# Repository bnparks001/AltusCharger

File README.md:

<div align="center">
  <h1>Altus Charger</h1>
  6 channel output charger for AltusMetrum batteries. 
  
  ## Status
  Boards have arrived and passed testing great!
  <div>
    <h3><em>Assembled Board:</em></h3>
    
  </div>
  
  ## Hardware
  This project is designed to support charging of 6 Altus Metrum batteries over a 5V 2A USB-C connection using the same battery charging circuit as the Telemega. Therefore, the RProg resistor selection was set to 3.3k to charge each battery at ~300mA. For context, the Telemega integrated charger is configured to charge at ~342mA. This results in ~13% slower charging per battery. However, with the benefit of charging multiple batteries at once this quickly makes up the difference.
  This project also includes a switch to turn off the LED indicators for overnight charging. 
  
  ## Schematic
  <h3><em>Root Schematic:</em></h3>
  <p>The root level schematic shows the overall blocking of the hardware design.</p>
  <br>
      
  ## PCB Design
  <div>
    <h3><em>3D Render:</em></h3>

  </div>
  
  <div>
    <h3><em>PCB Artwork:</em></h3>
    
    <br>
  </div>
</div>

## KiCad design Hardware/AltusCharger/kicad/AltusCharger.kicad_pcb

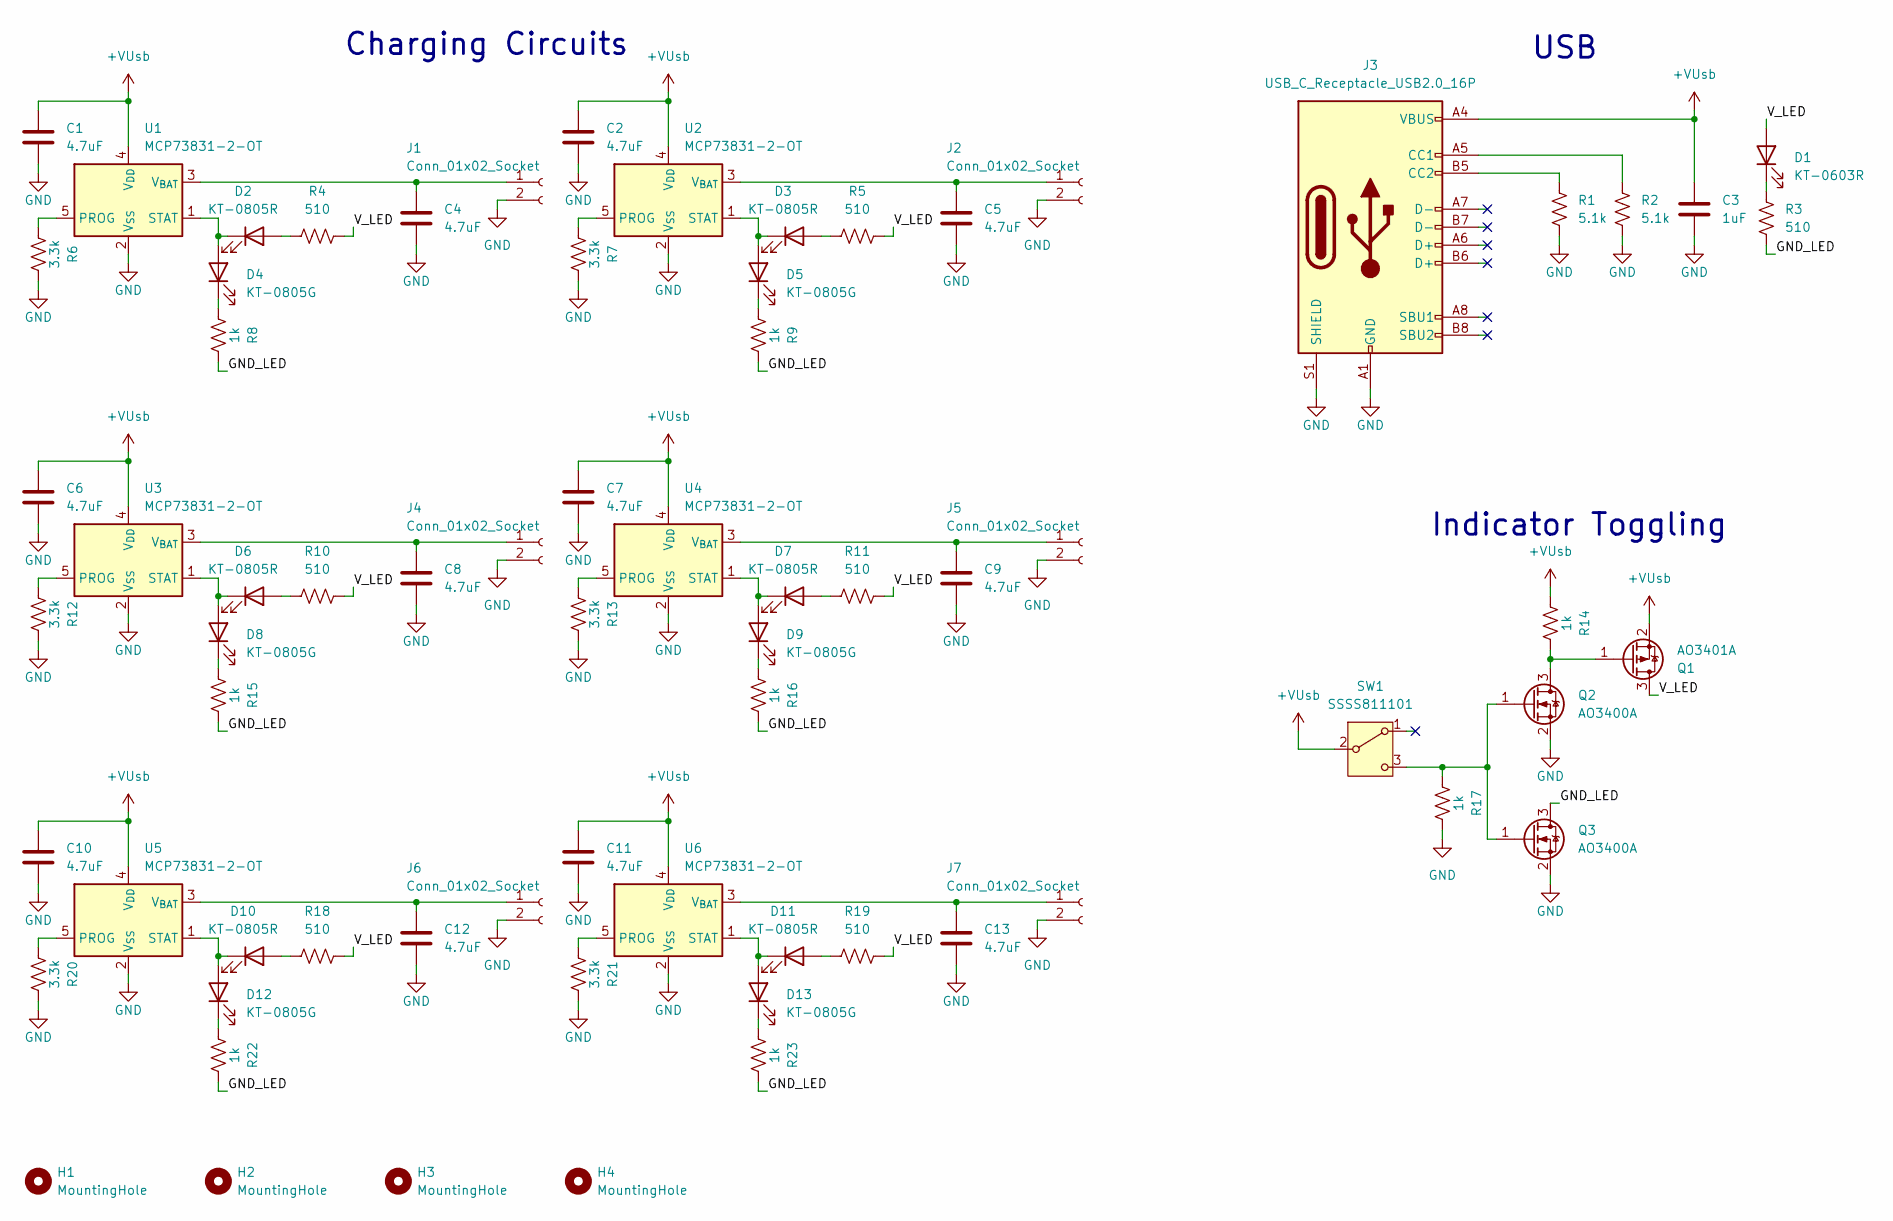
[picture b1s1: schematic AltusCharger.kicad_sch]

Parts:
C1, C2, C4, C5, C6, C7, C8, C9, C10, C11, C12, C13: 4.7uF; C_0402_1005Metric; JLCPCB Part # C23733
C3: 1uF; C_0402_1005Metric; JLCPCB Part # C52923
D1: KT-0603R; LED_0603_1608Metric; JLCPCB Part # C2286
D2, D3, D6, D7, D10, D11: KT-0805R; LED_0805_2012Metric; JLCPCB Part # C2295
D4, D5, D8, D9, D12, D13: KT-0805G; LED_0805_2012Metric; JLCPCB Part # C2297
H1, H2, H3, H4: MountingHole; MountingHole_3.2mm_M3
J1, J2, J4, J5, J6, J7: Conn_01x02_Socket; JST_PH_B2B-PH-K_1x02_P2.00mm_Vertical; JLCPCB Part # C2319
J3: USB_C_Receptacle_USB2.0_16P; USB_C_Receptacle_G-Switch_GT-USB-7010ASV; JLCPCB Part # C2988369
Q1: AO3401A; SOT-23; JLCPCB Part # C15127
Q2, Q3: AO3400A; SOT-23; JLCPCB Part # C20917
R1, R2: 5.1k; R_0402_1005Metric; JLCPCB Part # C25905
R3, R4, R5, R10, R11, R18, R19: 510; R_0402_1005Metric; JLCPCB Part # C25123
R6, R7, R12, R13, R20, R21: 3.3k; R_0402_1005Metric; JLCPCB Part # C25890
R8, R9, R14, R15, R16, R17, R22, R23: 1k; R_0402_1005Metric; JLCPCB Part # C11702
SW1: SSSS811101; SW_SSSS811101; JLCPCB Part # C109335
U1, U2, U3, U4, U5, U6: MCP73831-2-OT; SOT-23-5; JLCPCB Part # C424093

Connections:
+VUsb: C1.1, C2.1, C3.1, C6.1, C7.1, C10.1, C11.1, J3.A4 (VBUS), J3.A9 (VBUS), J3.B4 (VBUS), J3.B9 (VBUS), Q1.2 (S), R14.1, SW1.2 (B), U1.4 (V_{DD}), U2.4 (V_{DD}), U3.4 (V_{DD}), U4.4 (V_{DD}), U5.4 (V_{DD}), U6.4 (V_{DD})
/GND_LED: Q3.3 (D), R3.2, R8.2, R9.2, R15.2, R16.2, R22.2, R23.2
/V_LED: D1.2 (A), Q1.3 (D), R4.2, R5.2, R10.2, R11.2, R18.2, R19.2
GND: C1.2, C2.2, C3.2, C4.2, C5.2, C6.2, C7.2, C8.2, C9.2, C10.2, C11.2, C12.2, C13.2, J1.2, J2.2, J3.A1 (GND), J3.A12 (GND), J3.B1 (GND), J3.B12 (GND), J3.S1 (SHIELD), J4.2, J5.2, J6.2, J7.2, Q2.2 (S), Q3.2 (S), R1.2, R2.2, R6.2, R7.2, R12.2, R13.2, R17.2, R20.2, R21.2, U1.2 (V_{SS}), U2.2 (V_{SS}), U3.2 (V_{SS}), U4.2 (V_{SS}), U5.2 (V_{SS}), U6.2 (V_{SS})
unnamed: D1.1 (K), R3.1
unnamed: D2.2 (A), R4.1
unnamed: D2.1 (K), D4.2 (A), U1.1 (STAT)
unnamed: D3.2 (A), R5.1
unnamed: D3.1 (K), D5.2 (A), U2.1 (STAT)
unnamed: D4.1 (K), R8.1
unnamed: D5.1 (K), R9.1
unnamed: D6.2 (A), R10.1
unnamed: D6.1 (K), D8.2 (A), U3.1 (STAT)
unnamed: D7.2 (A), R11.1
unnamed: D7.1 (K), D9.2 (A), U4.1 (STAT)
unnamed: D8.1 (K), R15.1
unnamed: D9.1 (K), R16.1
unnamed: D10.2 (A), R18.1
unnamed: D10.1 (K), D12.2 (A), U5.1 (STAT)
unnamed: D11.2 (A), R19.1
unnamed: D11.1 (K), D13.2 (A), U6.1 (STAT)
unnamed: D12.1 (K), R22.1
unnamed: D13.1 (K), R23.1
unnamed: C4.1, J1.1, U1.3 (V_{BAT})
unnamed: C5.1, J2.1, U2.3 (V_{BAT})
unnamed: J3.A5 (CC1), R2.1
unnamed: J3.B5 (CC2), R1.1
unnamed: C8.1, J4.1, U3.3 (V_{BAT})
unnamed: C9.1, J5.1, U4.3 (V_{BAT})
unnamed: C12.1, J6.1, U5.3 (V_{BAT})
unnamed: C13.1, J7.1, U6.3 (V_{BAT})
unnamed: Q1.1 (G), Q2.3 (D), R14.2
unnamed: Q2.1 (G), Q3.1 (G), R17.1, SW1.3 (C)
unnamed: R6.1, U1.5 (PROG)
unnamed: R7.1, U2.5 (PROG)
unnamed: R12.1, U3.5 (PROG)
unnamed: R13.1, U4.5 (PROG)
unnamed: R20.1, U5.5 (PROG)
unnamed: R21.1, U6.5 (PROG)

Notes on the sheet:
USB
Charging Circuits
Indicator Toggling

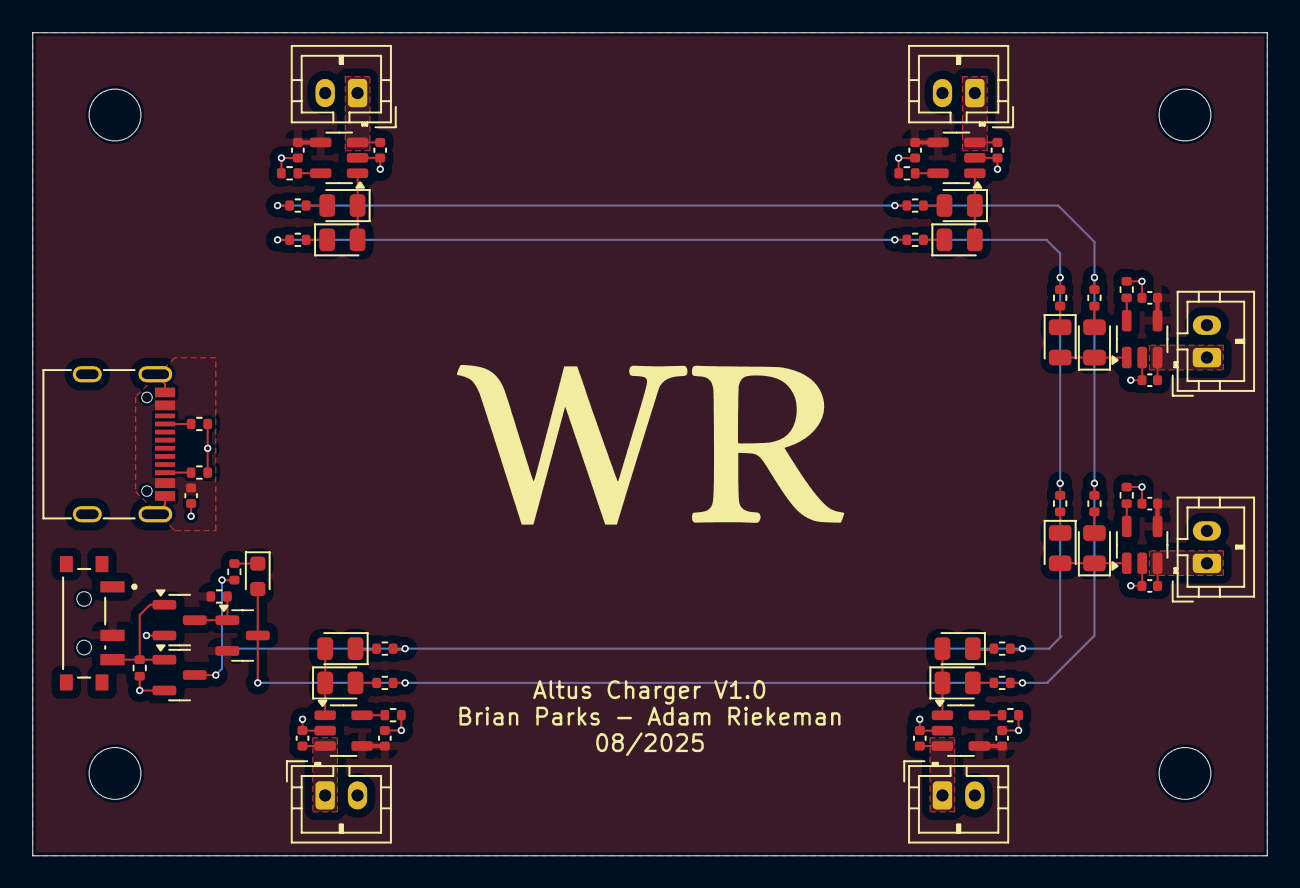
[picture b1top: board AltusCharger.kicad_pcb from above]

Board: 2 copper layers, 76.2 x 50.8 mm, 70 parts (0 on the bottom side), 39 nets.

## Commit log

2025-08-07 Added gitignore and workflow
2025-08-07 Did schematic
2025-08-07 Mounting holes for schematic
2025-08-07 Altus Charger V1.0
2025-08-07 Update autogen files
2025-08-07 Altus Charger changes to gen fab files
2025-08-07 Physical battery holder
2025-08-20 Updated documentation
2025-08-20 Updated image path
2025-08-20 Might actually be fixed now
2026-01-15 Updated to new resource gen and forced regen
2026-01-15 Helps to save that change
